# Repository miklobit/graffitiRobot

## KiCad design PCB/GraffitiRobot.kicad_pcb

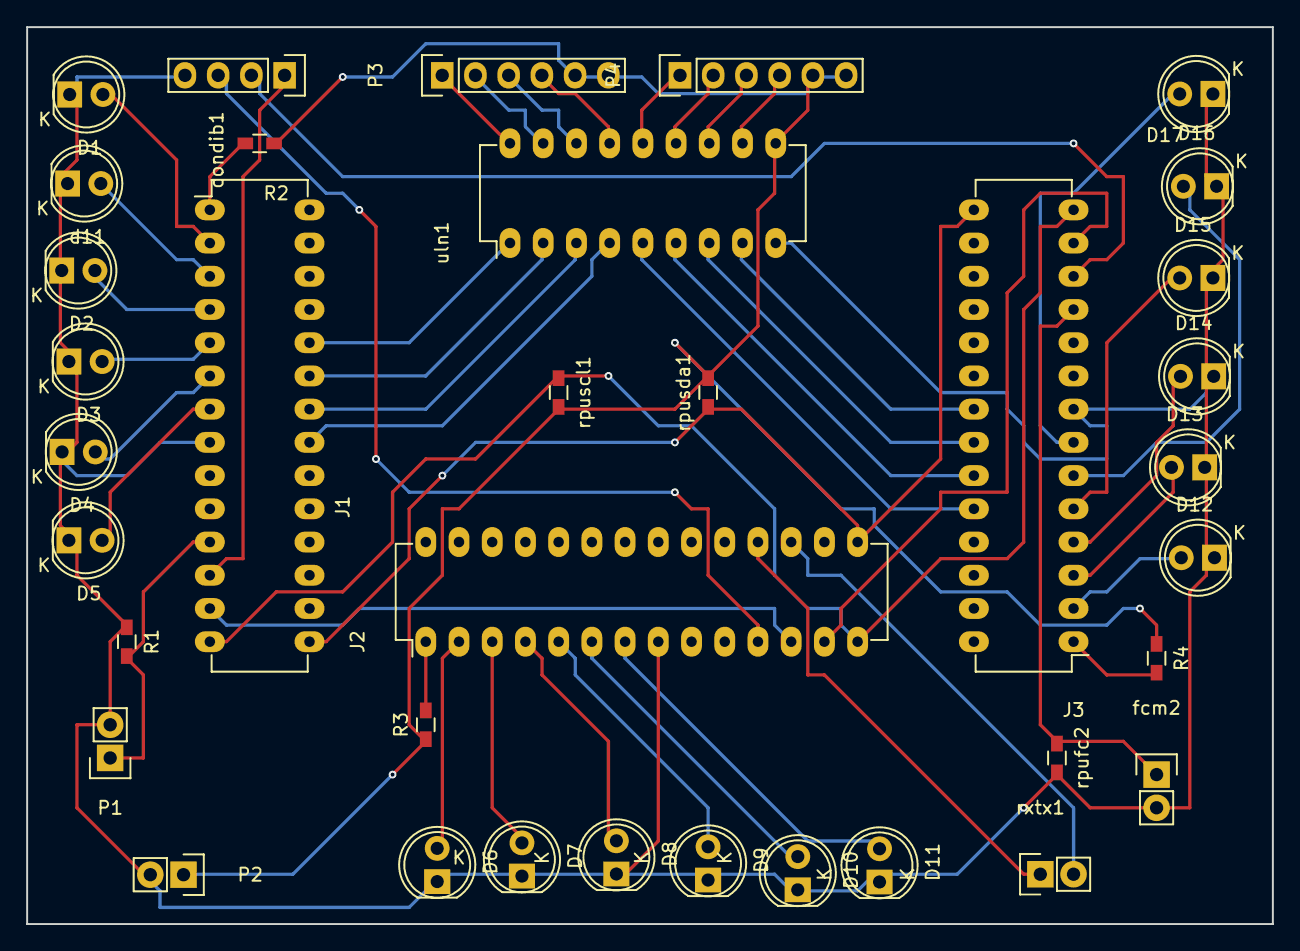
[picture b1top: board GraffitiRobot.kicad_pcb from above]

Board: 2 copper layers, 95.2 x 68.6 mm, 36 parts (0 on the bottom side), 50 nets.

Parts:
D1: d11; LED-5MM
D2: d13; LED-5MM
D3: d14; LED-5MM
D4: d15; LED-5MM
D5: d16; LED-5MM
D6: dm1; LED-5MM
D7: dm2; LED-5MM
D8: dm3; LED-5MM
D9: dm4; LED-5MM
D10: dm5; LED-5MM
D11: dm6; LED-5MM
D12, D13, D14, D15, D16, D17: LED; LED-5MM
J1: slave1; DIP-28_W7.62mm_LongPads
J2: masteer; DIP-28_W7.62mm_LongPads
J3: slave2; DIP-28_W7.62mm_LongPads
P1, P2: CONN_01X02; Pin_Header_Straight_1x02
P3: pap1; Pin_Header_Straight_1x06
P4: pap2; Pin_Header_Straight_1x06
R1: R; R_0603_HandSoldering
R2: rpusl1; R_0603_HandSoldering
R3: rpum; R_0603_HandSoldering
R4: rpusl2; R_0603_HandSoldering
condib1: conndib; Pin_Header_Straight_1x04
d11: d12; LED-5MM
fcm2: fcm2; Pin_Header_Straight_1x02
rpufc2: rpufc2; R_0603_HandSoldering
rpuscl1: rpuscl; R_0603_HandSoldering
rpusda1: rpusda; R_0603_HandSoldering
rxtx1: rtmaster; Socket_Strip_Straight_1x02
uln1: uln; DIP-18_W7.62mm_LongPads

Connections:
unnamed: D1.1, D2.1, D3.1, D4.1, D5.1, D6.1, D7.1, D8.1, D9.1, D10.1, D11.1, D12.1, D13.1, D14.1, D15.1, D16.1, D17.1, J1.8, J2.8, J3.8, P1.2, P2.2, R1.1, condib1.4, d11.1, fcm2.2, rpufc2.2, uln1.9
unnamed: D1.2, J1.2
unnamed: D2.2, J1.4
unnamed: D3.2, J1.5
unnamed: D4.2, J1.6
unnamed: D5.2, J1.7
unnamed: D6.2, J2.2
unnamed: D7.2, J2.3
unnamed: D8.2, J2.4
unnamed: D9.2, J2.5
unnamed: D10.2, J2.6
unnamed: D11.2, J2.7
unnamed: D12.2, J3.2
unnamed: D13.2, J3.3
unnamed: D14.2, J3.4
unnamed: D15.2, J3.5
unnamed: D16.2, J3.6
unnamed: D17.2, J3.7
unnamed: J1.1, R2.2
unnamed: J1.3, d11.2
unnamed: J1.11, P1.1, R1.2
unnamed: J1.12, condib1.1
unnamed: J1.13, J2.12
unnamed: J1.14, J2.14, J3.14, rpuscl1.1
unnamed: J1.15, J2.15, J3.15, rpusda1.1
unnamed: J1.21, uln1.4
unnamed: J1.22, uln1.3
unnamed: J1.23, uln1.2
unnamed: J1.24, uln1.1
unnamed: J2.1, R3.2
unnamed: J2.11, condib1.3
unnamed: J2.13, J3.13
unnamed: J2.17, rxtx1.2
unnamed: J2.18, rxtx1.1
unnamed: J3.1, R4.2
unnamed: J3.11, fcm2.1, rpufc2.1
unnamed: J3.12, condib1.2
unnamed: J3.21, uln1.8
unnamed: J3.22, uln1.7
unnamed: J3.23, uln1.6
unnamed: J3.24, uln1.5
unnamed: P2.1, P3.5, P3.6, P4.5, P4.6, R2.1, R3.1, R4.1, rpuscl1.2, rpusda1.2, uln1.10
unnamed: P3.1, uln1.18
unnamed: P3.2, uln1.17
unnamed: P3.3, uln1.16
unnamed: P3.4, uln1.15
unnamed: P4.1, uln1.14
unnamed: P4.2, uln1.13
unnamed: P4.3, uln1.12
unnamed: P4.4, uln1.11

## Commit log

2016-07-06 :octocat: Added .gitattributes & .gitignore files
2016-07-06 Proteus project created
2016-07-07 proteus circuit done
2016-07-08 UART tested
2016-07-09 I2C working - energized and de-enrgized
2016-07-10 homing tested
2016-07-15 Control de Posicion Implementado
2016-07-15 ensamble solidworks del sistema
2016-07-16 actualizacion de constantes para las consideraciones geometricas
2016-07-18 desarrollo de PCB
2016-07-19 informe added
2016-08-03 Version final
